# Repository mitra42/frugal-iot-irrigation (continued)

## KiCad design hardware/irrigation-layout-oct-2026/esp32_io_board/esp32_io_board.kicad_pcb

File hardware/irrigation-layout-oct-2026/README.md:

# Frugal-IoT Irrigation V0.2 — valve-driver board (branch `uln2803`)

> **This branch replaces the V0.1 board's four relays with MOSFETs driving 12 V DC solenoid valves directly**
> (DECISIONS D67–D78; a ULN2803A was tried first and dropped, D70). Eight valve outputs, D75. Phase 1 (schematic,
> BOM, cost) and Phase 2 (layout, D79–D86) are done, and the power parts now match the LoRa board (D87–D90): the
> PCB, PCB-LAYOUT.pdf and `fabrication/` are the valve board, laid out, routed and DRC clean (21 Nov 2026),
> **for review — not yet ordered or built**.

An ESP32 I/O board for irrigation and similar field control: eight 12 V DC valve outputs, RS485 (Modbus), I2C sensors,
two spare GPIOs, and power from 12 V, USB or a single LiPo cell. Designed Oct 2026 for assembly by JLCPCB.
This folder is for review: comments and suggested changes welcome — see "Points for reviewers" below.

## The board

- 100 × 62 mm (the relay board was 100 × 80), 2 layers, 1.6 mm FR-4, 4 × M3 corner holes.
- The eight valve terminals (5.08 mm, butted into one 81 mm row) along the bottom long edge, each channel's MOSFET,
  flyback diode and LED in a column straight above its terminal; 12 V in on the left edge beside them; field
  connectors (RS485, I2C, GPIOs, OLED) along the top edge; USB-C on the right short edge, LiPo connector on the left.
- The valve current has its own copper (D82): 2 mm from the 12 V terminal through the fuse and diode, a 2 mm
  +12V bus on the bottom layer along the terminal row, and 1 mm from each MOSFET straight down to its terminal.
- Surface-mount parts on the top side, assembled by JLCPCB; terminals and headers are through-hole
  (JLCPCB hand-solders them, or you can).

## Power

- Powered from **12 V** (screw terminal, up to 15 V), **5 V USB-C**, or a **local single LiPo cell** (optional,
  JST-PH, 18650 at most).
- 12 V input: 3 A resettable fuse, reverse-polarity protection (5 A Schottky), 15 V TVS, then a 5 V buck (AP63205). USB 5 V and the
  buck output are diode-ORed onto the 5 V rail, so either or both can be connected.
- The 5 V rail charges the cell (TP4056; 250 mA, or 500 mA with a solder jumper). The cell has its own
  protection (XB5353A, one chip with its MOSFETs inside: over-charge 4.30 V, over-discharge 2.4 V,
  3 A over-current/short), as on the LoRa board.
- Load sharing: when 5 V is present it powers the board and the charger only charges; when 5 V goes away a
  P-FET switches the cell in. Either source then feeds a 3.3 V LDO (RT9080, 600 mA, 2 µA quiescent) for the
  module.
- Two switched rails turned on together by one GPIO: **3V3_SW** (sensors, I2C, RS485) and **5V_SW** (RS485
  sensor supply). Both off at reset. 5V_SW only exists when 12 V or USB is present, not on battery alone.
- Monitoring: the 12 V input and the cell voltage are each read on an ADC pin.
- The valves run from 12 V, so **valves work only when 12 V is connected**.
- Test pads TP1–TP9 on every supply rail (+12V, +5V, VBUS, VBAT, VSYS, +3V3, +3V3_SW, +5V_SW) and GND, each
  labelled on the silkscreen with its rail, for a meter probe or a soldered wire.

## Processor

- ESP32-C6-MINI-1U module (default) or ESP32-C3-MINI-1U on the same footprint — both have a **U.FL antenna
  socket** (an external antenna is needed). Two pairs of 0 Ω links select which module's USB pins are used.
- Native USB on USB-C for programming and serial (no USB-UART chip); USB ESD protection.
- Buttons: RESET, BOOT/BTN1 (hold at reset for download mode, a normal button afterwards), BTN2 (C6 only).
- Status LED (green); charger LEDs (charging red, charged green).
- Unfitted headers for UART0 debug and a cell thermistor.

## Outputs and interfaces

- **8 valve outputs** for 12 V DC solenoid valves (channels 5–8 can be left unfitted to save ~$0.21–0.29 each), each a 2-way 5.08 mm terminal: V+ (+12V) and OUT (switched
  to ground). One AO3400A MOSFET per valve with a 100k gate pull-down and an SS34 flyback diode returned to
  the same +12V as the V+ pins (D69, D73). **Up to ~2 A per valve**, any number at once; total from 12 V IN
  limited to ~3 A by the input fuse F1 (D77). Fit an inline fuse at the battery too. Pumps can be driven too. Not for latching (pulse) valves or 24 V AC
  valves. Driven through an I2C I/O expander (TCA9534); the pull-downs keep the valves off through reset
  and boot. A red LED per valve shows it is on.
- **RS485** (Modbus): 3.3 V transceiver, not isolated, transmit/receive switched automatically from the TX
  line; bias resistors, 120 Ω termination on a solder jumper, surge protection. Terminal: 5V_SW, A, B, GND.
- **I2C**: 4-way 2.54 mm terminal (3V3_SW, SDA, SCL, GND) plus a 4-pin OLED header (GND, 3V3_SW, SCL, SDA).
- **2 GPIOs** (GPIO_A — ADC capable — and GPIO_B, C6 only) on 2-way 2.54 mm terminals with GND, with
  unfitted pull-up/pull-down positions.

## Firmware notes

- Turn on RAIL_EN before any I2C traffic (valve changes included) or RS485; the expander itself is always
  powered and keeps the valves as set while the rail is off.
- Valve outputs: TCA9534 P0–P7 high = valve 1–8 on (P0–P3 as on the relay board, so no firmware change for those). Terminals J11–J18; RS485 is now J10.
- GPIO map (module pad → use) is in DECISIONS.md, D18.

## Points for reviewers

Items that are deliberately "proposed" rather than final — opinions especially welcome:

1. RS485 direction from TX (D21): fine for Modbus at 9600 baud, marginal with long cables and two
   terminations; a true auto-direction transceiver (THVD1406) is the alternative.
2. RS485 terminal supplies 5V_SW — should it be 12 V for your sensors? (D22)
3. Cell thermistor (TEMP) disabled by default (D27); charge current 250/500 mA (D12).
4. LiPo connector: pin 1 = −, pin 2 = + (D47). JST-PH polarity is not standard — check your cells.
5. Valve outputs (D73): ~2 A per valve, ~3 A total from 12 V IN, where F1, a 3 A resettable fuse, trips on a short (D77). Enough for your valves
   and any pump?
6. The 5.08 mm terminals use the Phoenix MKDS footprint for KF128 parts of the same pitch (D42).
7. Small bulk capacitance on 3V3_SW to limit inrush (D33).
8. Before ordering: check part rotations in JLCPCB's assembly preview (see fabrication/README.md).

## Cost (JLCPCB, Nov 2026)

About **$21.04 per board for 10**, **$12.07 per board for 100**, assembled, before shipping, with all eight
valve channels fitted and the input fuse (JLCPCB prices of 21 Nov 2026; the four-relay design is $22.04 / $12.63).
The bare PCB for the 100 × 62 mm board is estimated from the 100 × 80 mm quote, not yet re-quoted (D86): the
smaller board saves nothing at 10 and about $0.13 per board at 100.
Breakdown in COST-ESTIMATE.txt; the ESP32 module is the largest single item.

## What's in this folder

| | |
|---|---|
| `README.md` | This description |
| `SCHEMATIC.pdf` | Full schematic, one sheet |
| `PCB-LAYOUT.pdf` | 3D views and both copper layers |
| `BOM.csv` | Bill of materials with LCSC (JLCPCB) part numbers |
| `COST-ESTIMATE.txt` | JLCPCB cost for 10 and 100 boards |
| `DECISIONS.md` | Every design decision, why, and what would reopen it (D1–D90) |
| `esp32_io_board/` | KiCad 10 project (schematic, PCB, project libraries) |
| `fabrication/` | Files to order from JLCPCB — see its README |
| `firmware/` | PlatformIO env for frugal-iot-irrigation + board variant (pins_arduino.h) |
| `datasheets/` | Datasheets checked during design |
| `claude-tools/` | Scripts Claude uses to regenerate and change the design — reviewers can ignore |

To suggest a change: mark up the PDFs, edit in KiCad, or describe it; the schematic is generated from
`claude-tools/schematic/circuit.py`, so changes made by Claude go there rather than into the .kicad_sch.

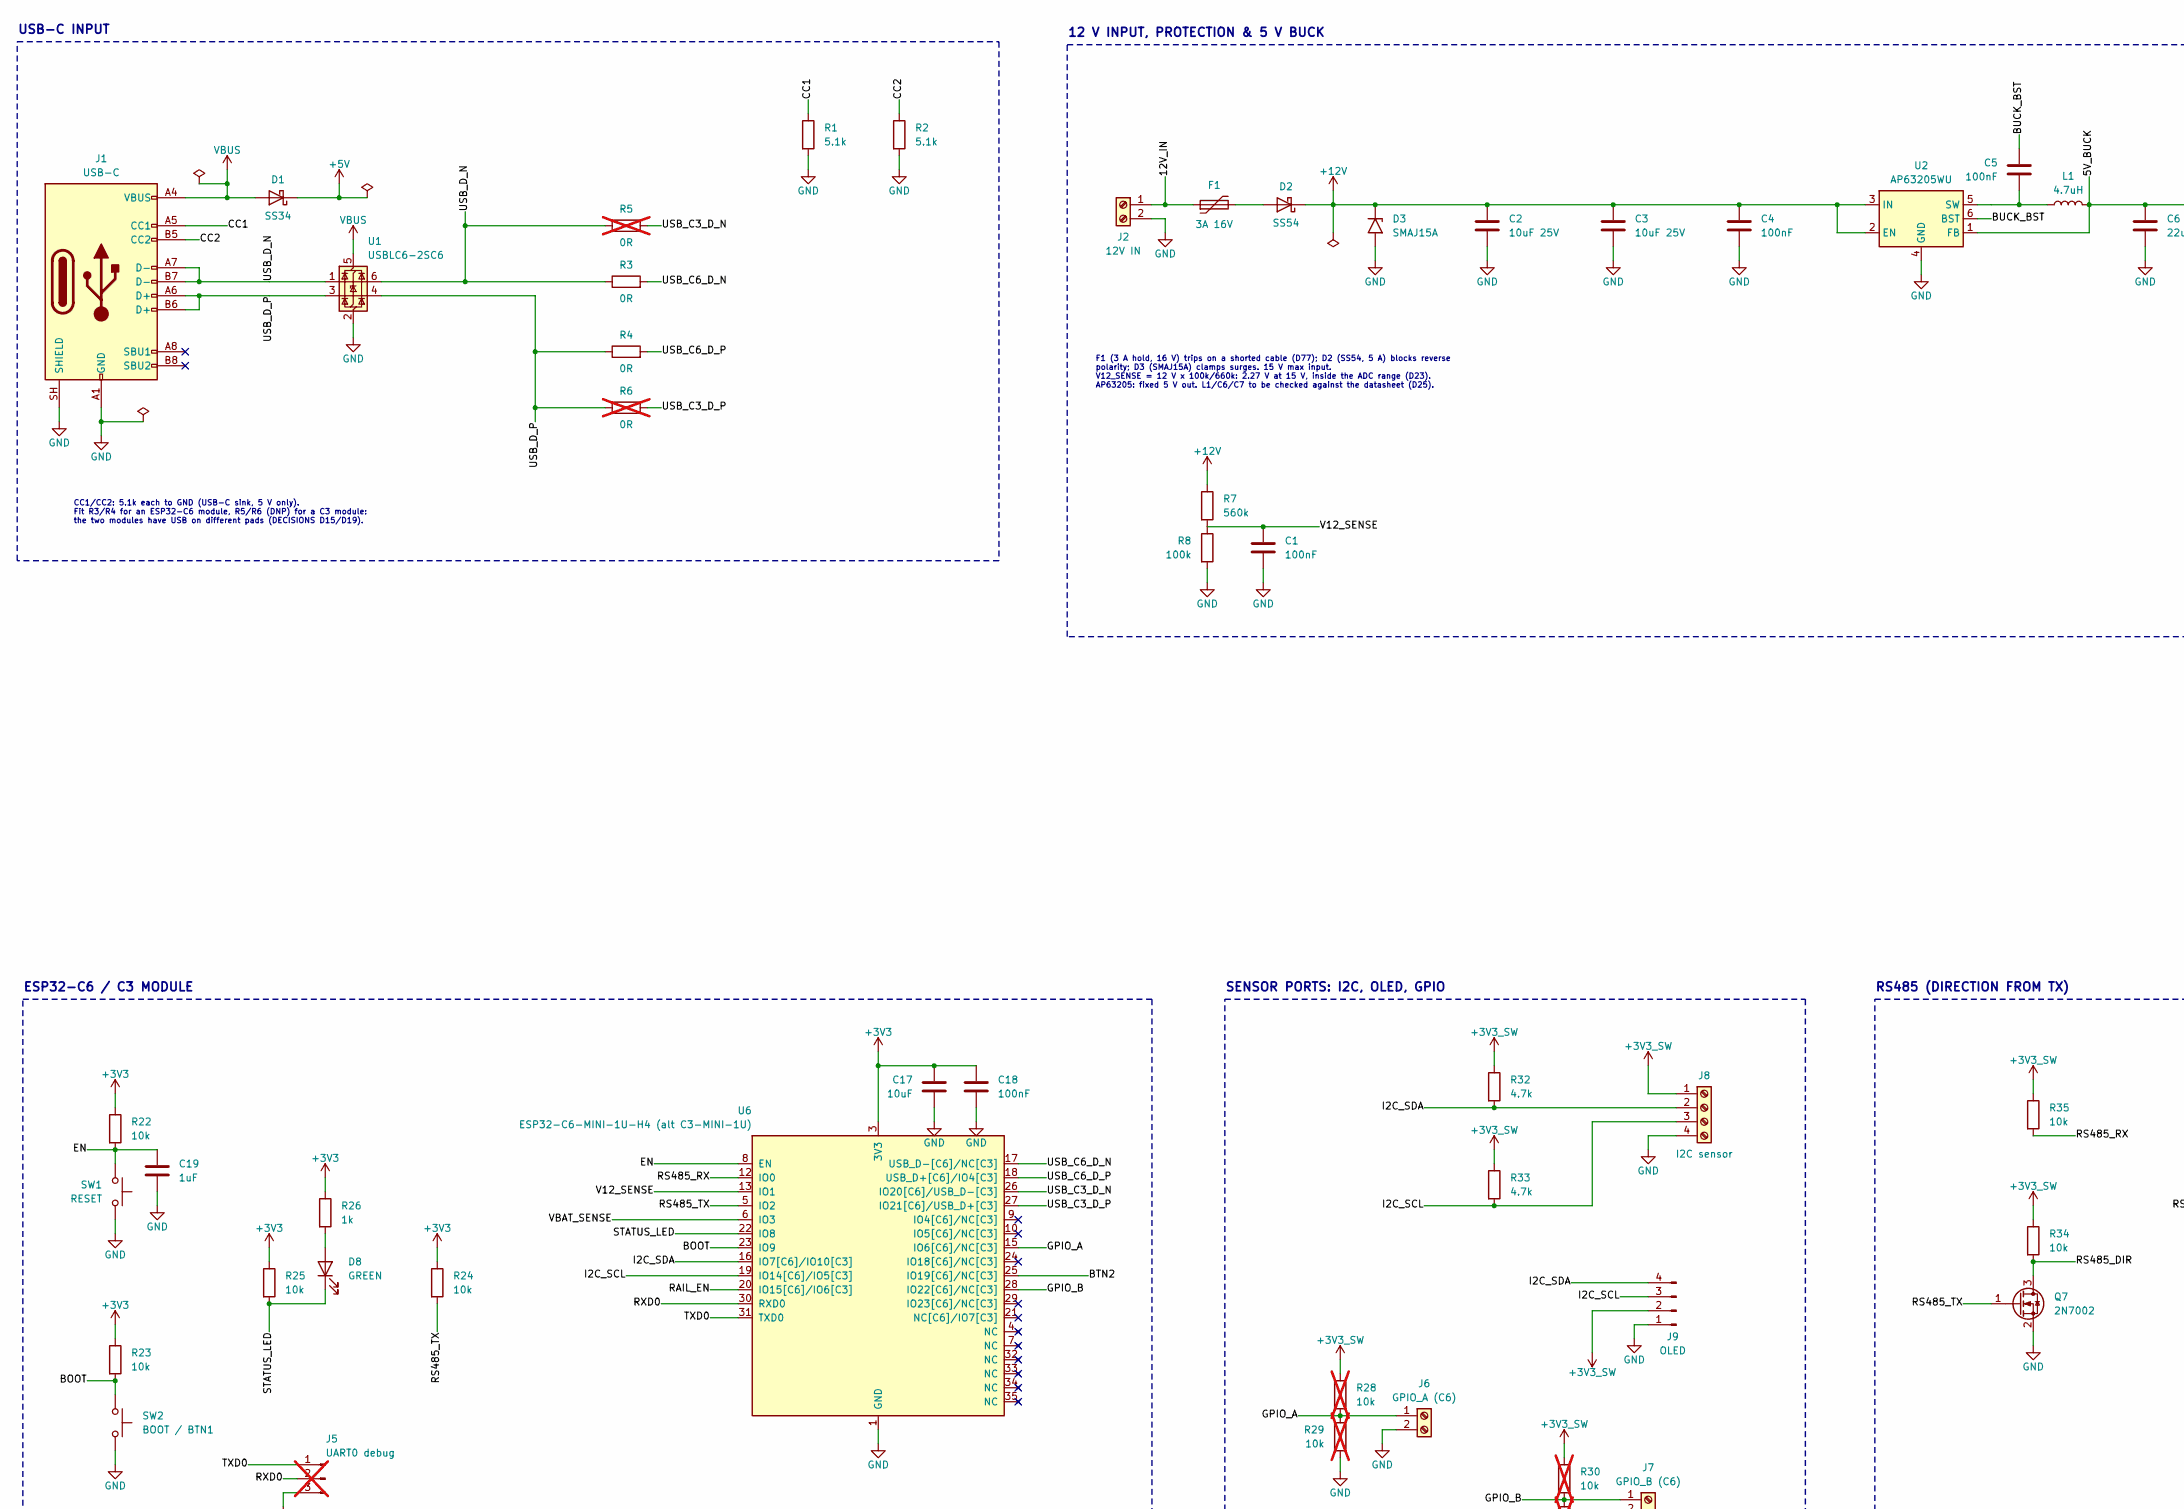
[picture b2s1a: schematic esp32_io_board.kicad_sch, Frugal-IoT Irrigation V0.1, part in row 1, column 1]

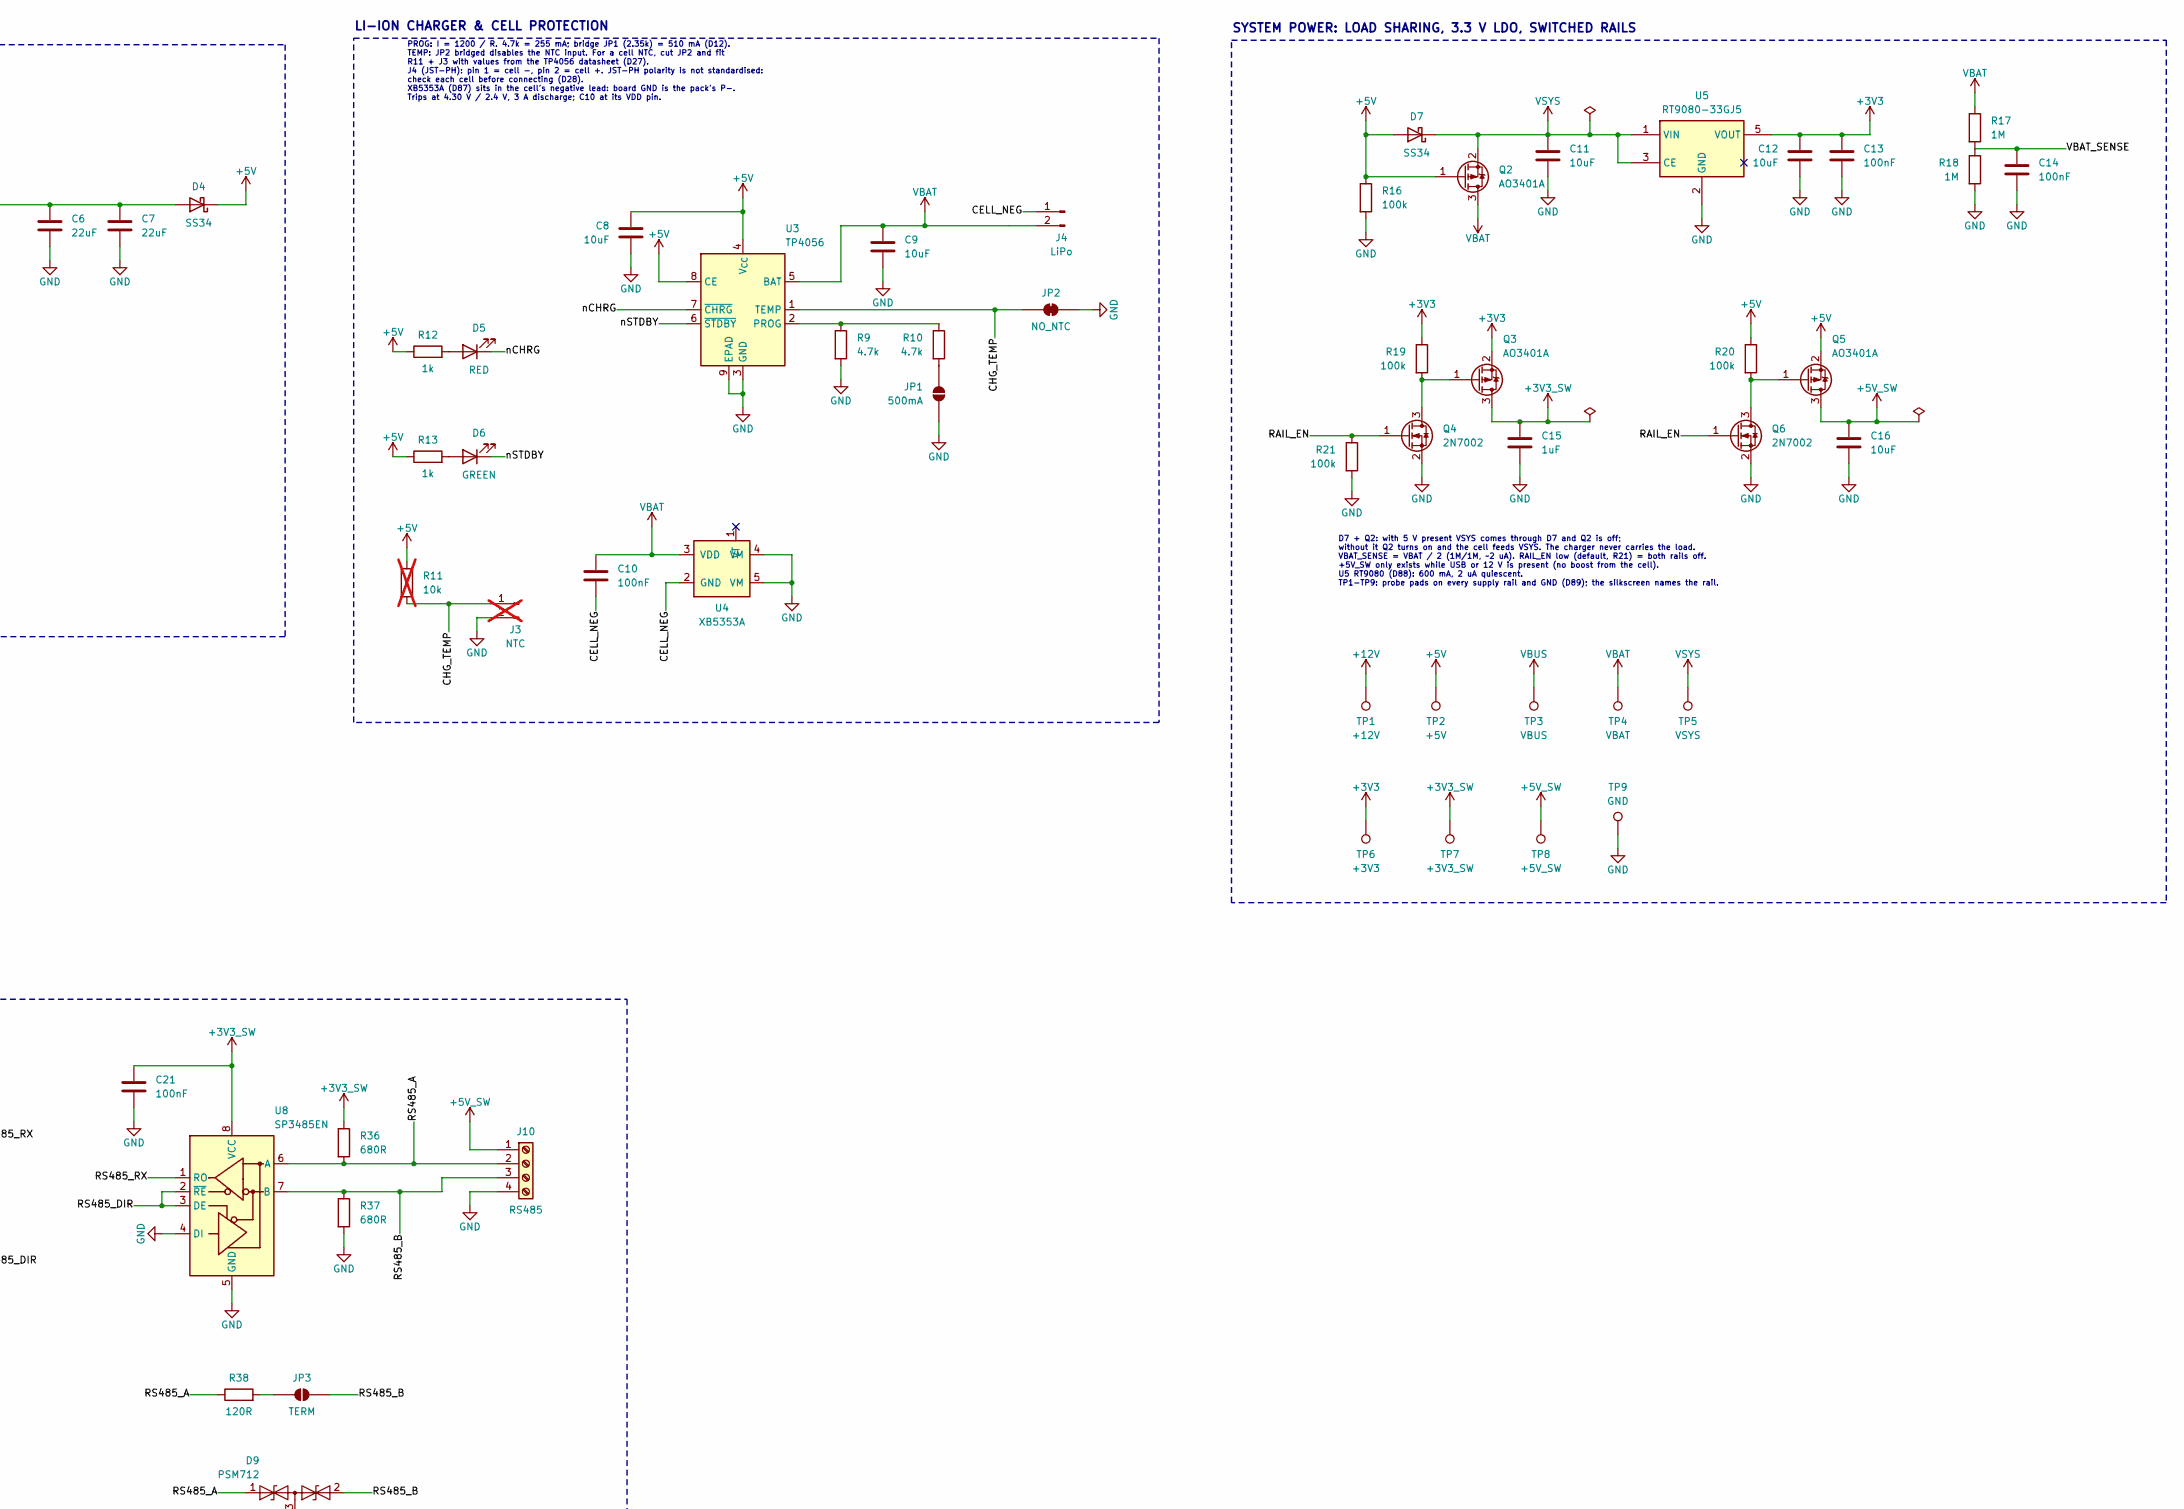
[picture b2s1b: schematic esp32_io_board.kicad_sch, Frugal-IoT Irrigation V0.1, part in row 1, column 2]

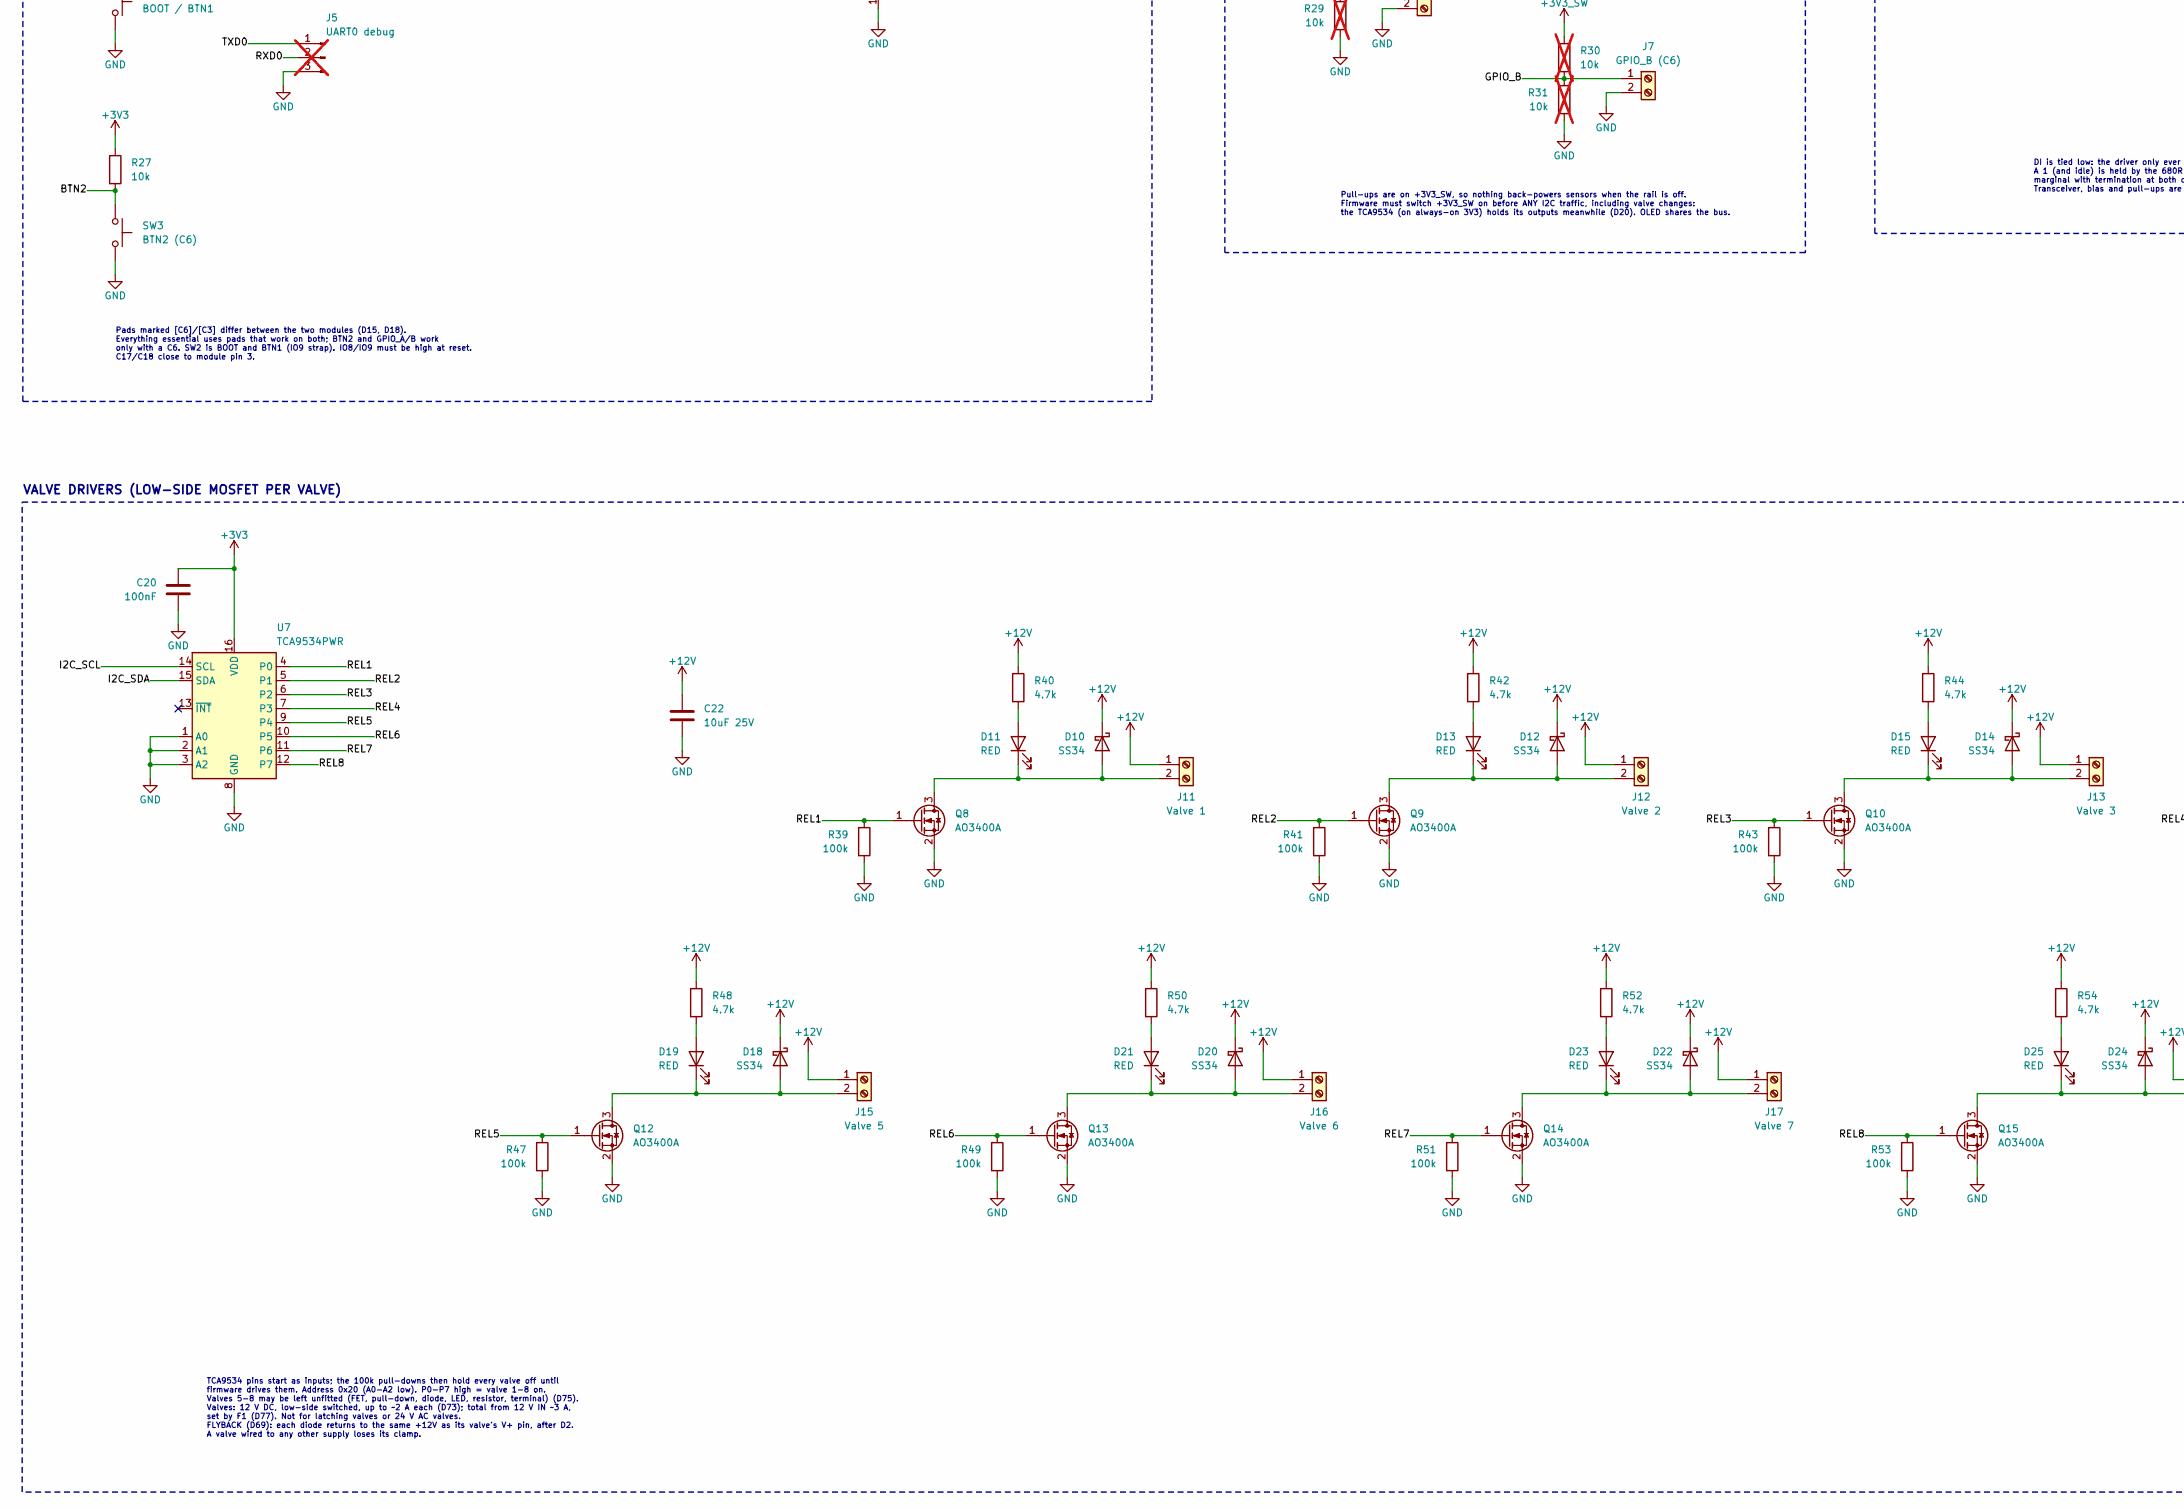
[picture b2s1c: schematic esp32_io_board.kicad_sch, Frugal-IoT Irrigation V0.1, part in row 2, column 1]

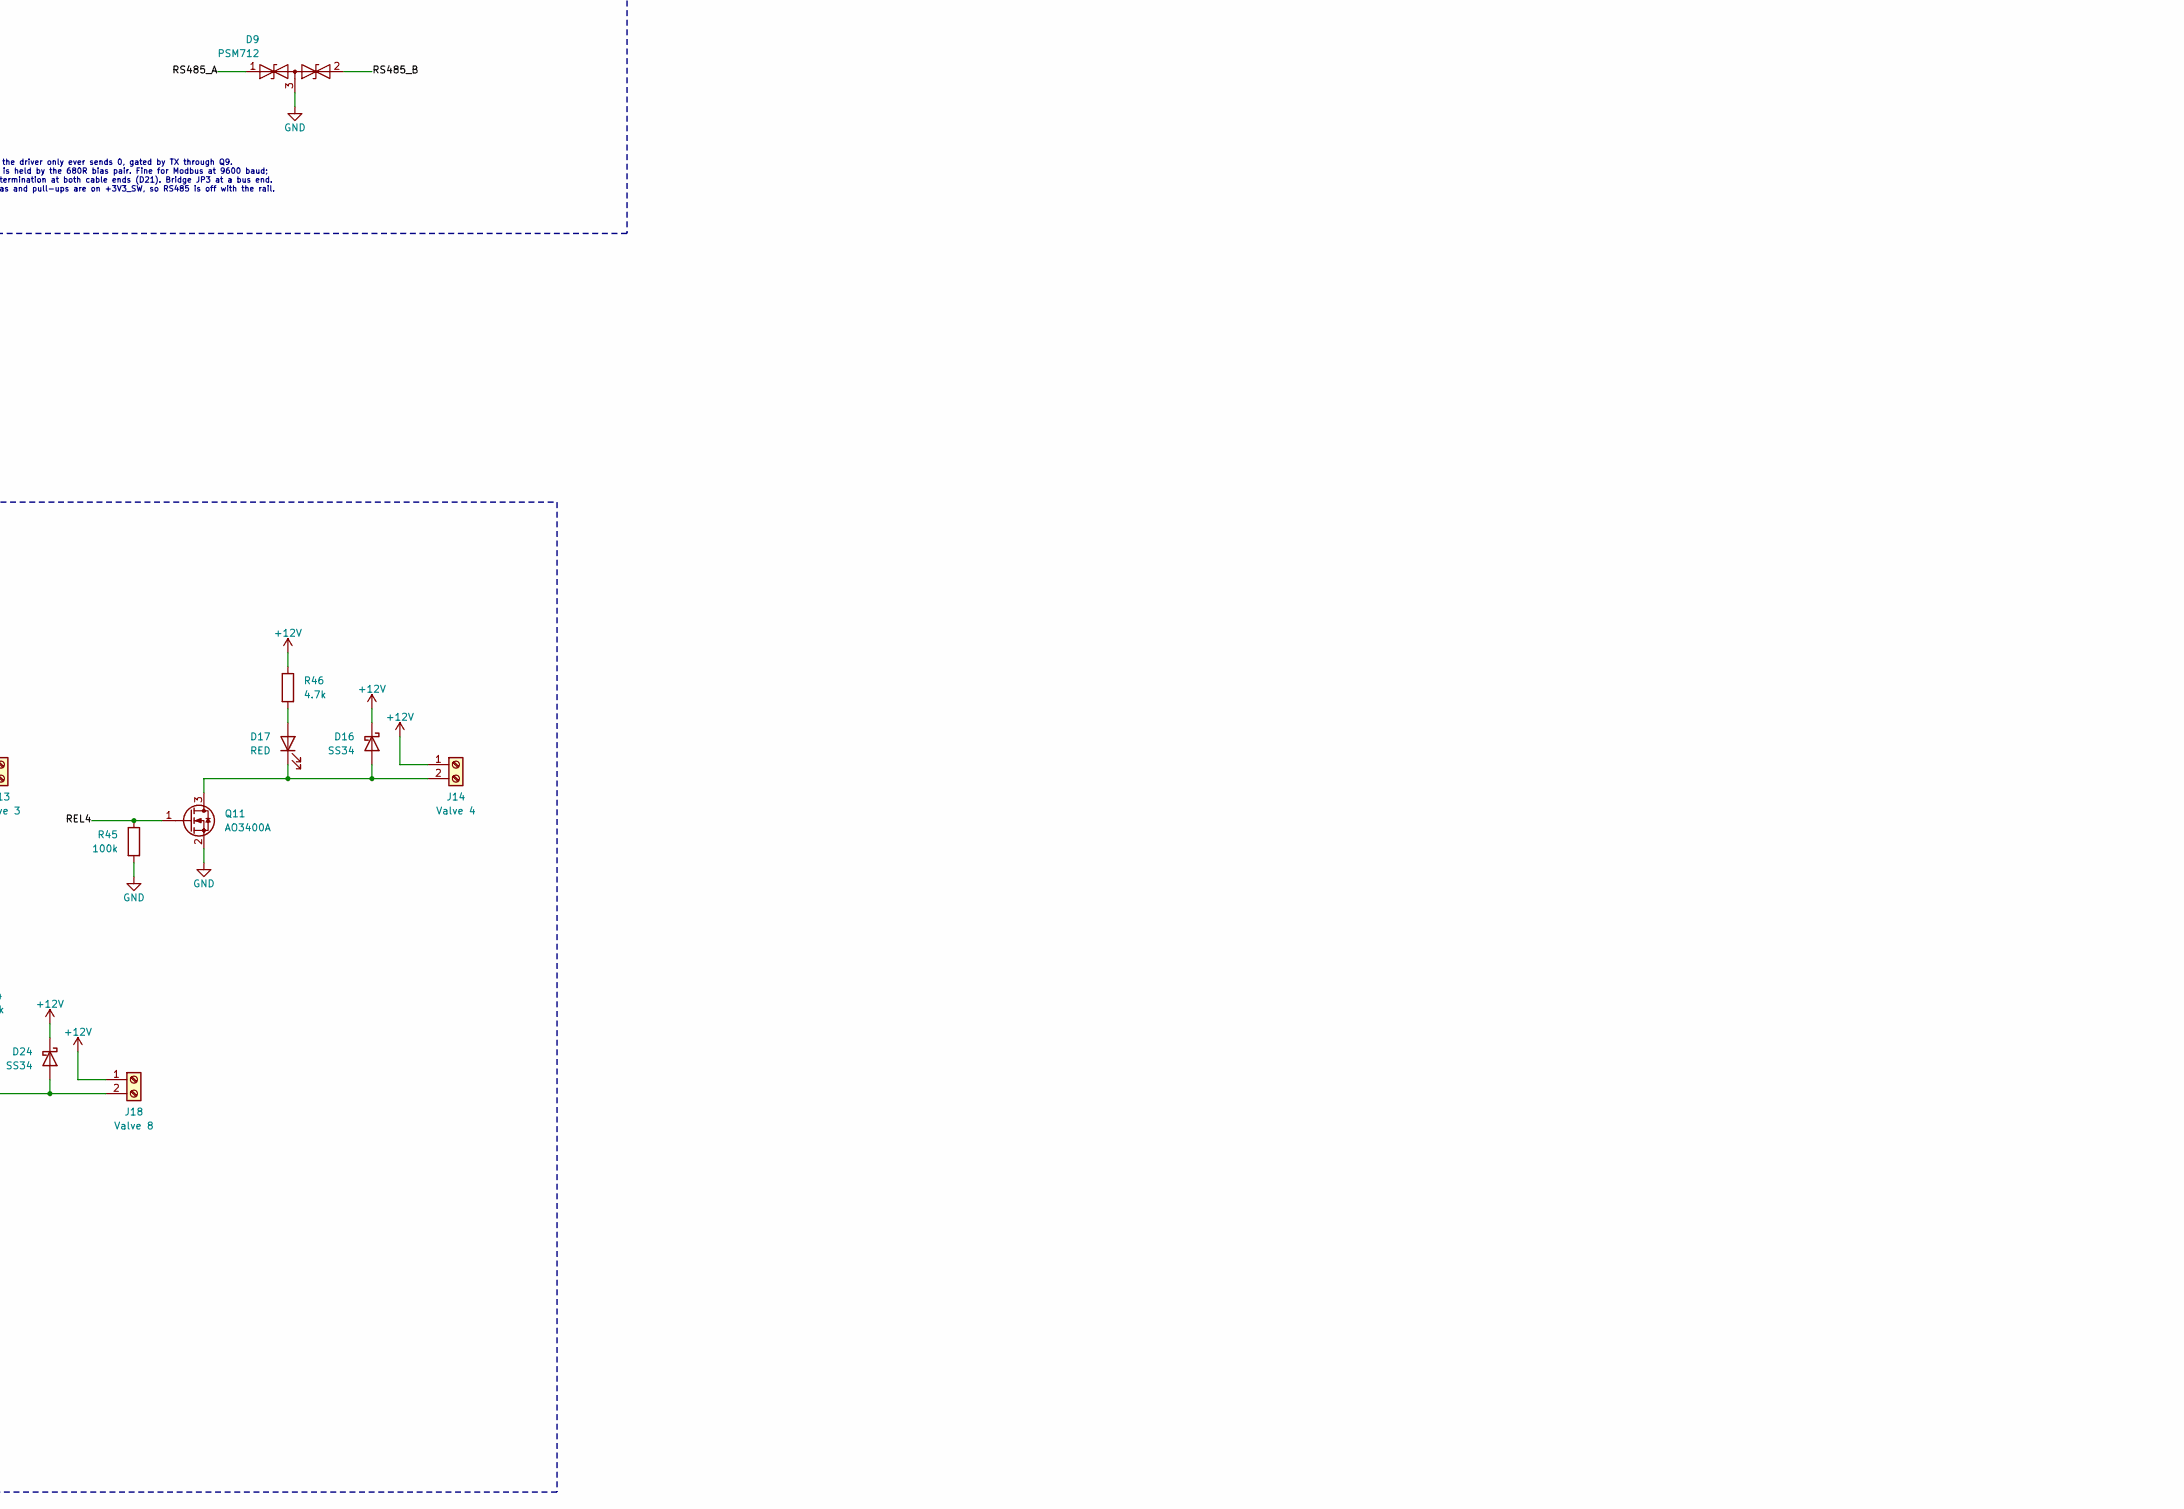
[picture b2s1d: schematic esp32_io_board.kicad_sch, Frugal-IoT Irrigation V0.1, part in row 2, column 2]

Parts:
C1, C4, C5, C10, C13, C14, C18, C20, C21: 100nF; C_0603_1608Metric; MPN 100nF; LCSC C14663
C2, C3, C22: 10uF 25V; C_1206_3216Metric; MPN 10uF 25V; LCSC C13585
C6, C7: 22uF; C_1206_3216Metric; MPN 22uF; LCSC C12891
C8, C9, C11, C12, C16, C17: 10uF; C_0603_1608Metric; MPN 10uF; LCSC C19702
C15, C19: 1uF; C_0603_1608Metric; MPN 1uF; LCSC C15849
D1, D4, D7, D10, D12, D14, D16, D18, D20, D22, D24: SS34; D_SMA; MPN SS34; LCSC C8678
D2: SS54; D_SMA; MPN SS54; LCSC C22452
D3: SMAJ15A; D_SMA; MPN SMAJ15A; LCSC C19077535
D5, D11, D13, D15, D17, D19, D21, D23, D25: RED; LED_0603_1608Metric; MPN KT-0603R; LCSC C2286
D6, D8: GREEN; LED_0805_2012Metric; MPN KT-0805G; LCSC C2297
D9: PSM712; SOT-23; MPN PSM712-LF-T7; LCSC C32677
F1: 3A 16V; Fuse_1812_4532Metric; MPN SMD1812P300TF/16; LCSC C702820
J1: USB-C; USB_C_Receptacle_HRO_TYPE-C-31-M-12; MPN TYPE-C-31-M-12; LCSC C165948
J2: 12V IN; TerminalBlock_KF128-5.08-2P; MPN KF128-5.08-2P; LCSC C474952
J3: NTC; PinHeader_1x02_P2.54mm_Vertical; MPN NTC; not fitted
J4: LiPo; JST_PH_S2B-PH-K_1x02_P2.00mm_Horizontal; MPN S2B-PH-K-S; LCSC C157932
J5: UART0 debug; PinHeader_1x03_P2.54mm_Vertical; MPN UART0 debug; not fitted
J6: GPIO_A (C6); TerminalBlock_Xinya_XY308-2.54-2P_1x02_P2.54mm_Horizontal; MPN XY308-2.54-2P; LCSC C557685
J7: GPIO_B (C6); TerminalBlock_Xinya_XY308-2.54-2P_1x02_P2.54mm_Horizontal; MPN XY308-2.54-2P; LCSC C557685
J8: I2C sensor; TerminalBlock_Xinya_XY308-2.54-4P_1x04_P2.54mm_Horizontal; MPN XY308-2.54-4P; LCSC C915913
J9: OLED; PinHeader_1x04_P2.54mm_Vertical; MPN PZ254V-11-04P; LCSC C492403
J10: RS485; TerminalBlock_Xinya_XY308-2.54-4P_1x04_P2.54mm_Horizontal; MPN XY308-2.54-4P; LCSC C915913
J11: Valve 1; TerminalBlock_KF128-5.08-2P; MPN KF128-5.08-2P; LCSC C474952
J12: Valve 2; TerminalBlock_KF128-5.08-2P; MPN KF128-5.08-2P; LCSC C474952
J13: Valve 3; TerminalBlock_KF128-5.08-2P; MPN KF128-5.08-2P; LCSC C474952
J14: Valve 4; TerminalBlock_KF128-5.08-2P; MPN KF128-5.08-2P; LCSC C474952
J15: Valve 5; TerminalBlock_KF128-5.08-2P; MPN KF128-5.08-2P; LCSC C474952
J16: Valve 6; TerminalBlock_KF128-5.08-2P; MPN KF128-5.08-2P; LCSC C474952
J17: Valve 7; TerminalBlock_KF128-5.08-2P; MPN KF128-5.08-2P; LCSC C474952
J18: Valve 8; TerminalBlock_KF128-5.08-2P; MPN KF128-5.08-2P; LCSC C474952
JP1: 500mA; SolderJumper-2_P1.3mm_Open_RoundedPad1.0x1.5mm; MPN 500mA
JP2: NO_NTC; SolderJumper-2_P1.3mm_Bridged_RoundedPad1.0x1.5mm; MPN NO_NTC
JP3: TERM; SolderJumper-2_P1.3mm_Open_RoundedPad1.0x1.5mm; MPN TERM
L1: 4.7uH; L_Sunlord_SWPA5040S; MPN SWPA5040S4R7NT; LCSC C305174
Q2, Q3, Q5: AO3401A; SOT-23; MPN AO3401A; LCSC C15127
Q4, Q6, Q7: 2N7002; SOT-23; MPN 2N7002; LCSC C8545
Q8, Q9, Q10, Q11, Q12, Q13, Q14, Q15: AO3400A; SOT-23; MPN AO3400A; LCSC C20917
R1, R2: 5.1k; R_0603_1608Metric; MPN 5.1k; LCSC C23186
R3, R4: 0R; R_0603_1608Metric; MPN 0R; LCSC C21189
R5, R6: 0R; R_0603_1608Metric; MPN 0R; LCSC C21189; not fitted
R7: 560k; R_0603_1608Metric; MPN 560k; LCSC C23203
R8, R16, R19, R20, R21, R39, R41, R43, R45, R47, R49, R51, R53: 100k; R_0603_1608Metric; MPN 100k; LCSC C25803
R9, R10, R32, R33, R40, R42, R44, R46, R48, R50, R52, R54: 4.7k; R_0603_1608Metric; MPN 4.7k; LCSC C23162
R11, R28, R29, R30, R31: 10k; R_0603_1608Metric; MPN 10k; LCSC C25804; not fitted
R12, R13, R26: 1k; R_0603_1608Metric; MPN 1k; LCSC C21190
R17, R18: 1M; R_0603_1608Metric; MPN 1M; LCSC C22935
R22, R23, R24, R25, R27, R34, R35: 10k; R_0603_1608Metric; MPN 10k; LCSC C25804
R36, R37: 680R; R_0603_1608Metric; MPN 680R; LCSC C23228
R38: 120R; R_0603_1608Metric; MPN 120R; LCSC C22787
SW1: RESET; SW_Push_1P1T_XKB_TS-1187A; MPN TS-1187A-B-A-B; LCSC C318884
SW2: BOOT / BTN1; SW_Push_1P1T_XKB_TS-1187A; MPN TS-1187A-B-A-B; LCSC C318884
SW3: BTN2 (C6); SW_Push_1P1T_XKB_TS-1187A; MPN TS-1187A-B-A-B; LCSC C318884
TP1: +12V; TestPoint_Pad_D1.5mm; MPN +12V
TP2: +5V; TestPoint_Pad_D1.5mm; MPN +5V
TP3: VBUS; TestPoint_Pad_D1.5mm; MPN VBUS
TP4: VBAT; TestPoint_Pad_D1.5mm; MPN VBAT
TP5: VSYS; TestPoint_Pad_D1.5mm; MPN VSYS
TP6: +3V3; TestPoint_Pad_D1.5mm; MPN +3V3
TP7: +3V3_SW; TestPoint_Pad_D1.5mm; MPN +3V3_SW
TP8: +5V_SW; TestPoint_Pad_D1.5mm; MPN +5V_SW
TP9: GND; TestPoint_Pad_D1.5mm; MPN GND
U1: USBLC6-2SC6; SOT-23-6; MPN USBLC6-2SC6; LCSC C7519
U2: AP63205WU; TSOT-23-6; MPN AP63205WU-7; LCSC C2071056
U3: TP4056; SOIC-8-1EP_3.9x4.9mm_P1.27mm_EP2.41x3.3mm; MPN TP4056; LCSC C16581
U4: XB5353A; SOT-23-5; MPN XB5353A; LCSC C80628
U5: RT9080-33GJ5; TSOT-23-5; MPN RT9080-33GJ5; LCSC C841192
U6: ESP32-C6-MINI-1U-H4 (alt C3-MINI-1U); ESP32-C3-C6-MINI-1U; MPN ESP32-C6-MINI-1U-H4; LCSC C20627095
U7: TCA9534PWR; TSSOP-16_4.4x5mm_P0.65mm; MPN TCA9534PWR; LCSC C783615
U8: SP3485EN; SOIC-8_3.9x4.9mm_P1.27mm; MPN SP3485EN-L/TR; LCSC C8963

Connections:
+3V3: C12.1, C13.1, C17.1, C18.1, C20.1, Q3.2 (S), R19.1, R22.1, R23.1, R24.1, R25.1, R26.1, R27.1, TP6.1, U5.5 (VOUT), U6.3 (3V3), U7.16 (VDD)
/5V_BUCK: C6.1, C7.1, D4.2 (A), L1.2, U2.1 (FB)
/12V_IN: F1.1, J2.1
/BOOT: R23.2, SW2.1, U6.23 (IO9)
/BTN2: R27.2, SW3.1, U6.25 (IO19[C6]/NC[C3])
/BUCK_BST: C5.1, U2.6 (BST)
/CC1: J1.A5 (CC1), R1.1
/CC2: J1.B5 (CC2), R2.1
/CELL_NEG: C10.2, J4.1, U4.2 (GND)
/CHG_TEMP: J3.1, JP2.1 (A), R11.2, U3.1 (TEMP)
/EN: C19.1, R22.2, SW1.1, U6.8 (EN)
/GPIO_A: J6.1, R28.2, R29.1, U6.15 (IO6[C6]/NC[C3])
/GPIO_B: J7.1, R30.2, R31.1, U6.28 (IO22[C6]/NC[C3])
/I2C_SCL: J8.3, J9.3, R33.2, U6.19 (IO14[C6]/IO5[C3]), U7.14 (SCL)
/I2C_SDA: J8.2, J9.4, R32.2, U6.16 (IO7[C6]/IO10[C3]), U7.15 (SDA)
/RAIL_EN: Q4.1 (G), Q6.1 (G), R21.1, U6.20 (IO15[C6]/IO6[C3])
/REL1: Q8.1 (G), R39.1, U7.4 (P0)
/REL2: Q9.1 (G), R41.1, U7.5 (P1)
/REL3: Q10.1 (G), R43.1, U7.6 (P2)
/REL4: Q11.1 (G), R45.1, U7.7 (P3)
/REL5: Q12.1 (G), R47.1, U7.9 (P4)
/REL6: Q13.1 (G), R49.1, U7.10 (P5)
/REL7: Q14.1 (G), R51.1, U7.11 (P6)
/REL8: Q15.1 (G), R53.1, U7.12 (P7)
/RS485_A: D9.1 (A1), J10.2, R36.2, R38.1, U8.6 (A)
/RS485_B: D9.2 (A2), J10.3, JP3.2 (B), R37.1, U8.7 (B)
/RS485_DIR: Q7.3 (D), R34.2, U8.2 (~RE), U8.3 (DE)
/RS485_RX: R35.2, U6.12 (IO0), U8.1 (RO)
/RS485_TX: Q7.1 (G), R24.2, U6.5 (IO2)
/RXD0: J5.2, U6.30 (RXD0)
/STATUS_LED: D8.1 (K), R25.2, U6.22 (IO8)
/TXD0: J5.1, U6.31 (TXD0)
/USB_C3_D_N: R5.2, U6.26 (IO20[C6]/USB_D-[C3])
/USB_C3_D_P: R6.2, U6.27 (IO21[C6]/USB_D+[C3])
/USB_C6_D_N: R3.2, U6.17 (USB_D-[C6]/NC[C3])
/USB_C6_D_P: R4.2, U6.18 (USB_D+[C6]/IO4[C3])
/USB_D_N: J1.A7 (D-), J1.B7 (D-), R3.1, R5.1, U1.1 (I/O1), U1.6 (I/O1)
/USB_D_P: J1.A6 (D+), J1.B6 (D+), R4.1, R6.1, U1.3 (I/O2), U1.4 (I/O2)
/V12_SENSE: C1.1, R7.2, R8.1, U6.13 (IO1)
/VBAT_SENSE: C14.1, R17.2, R18.1, U6.6 (IO3)
/nCHRG: D5.1 (K), U3.7 (~CHRG)
/nSTDBY: D6.1 (K), U3.6 (~STDBY)
unnamed: D2.2 (A), F1.2
unnamed: D5.2 (A), R12.2
unnamed: D6.2 (A), R13.2
unnamed: D8.2 (A), R26.2
unnamed: D10.2 (A), D11.1 (K), J11.2, Q8.3 (D)
unnamed: D11.2 (A), R40.2
unnamed: D12.2 (A), D13.1 (K), J12.2, Q9.3 (D)
unnamed: D13.2 (A), R42.2
unnamed: D14.2 (A), D15.1 (K), J13.2, Q10.3 (D)
unnamed: D15.2 (A), R44.2
unnamed: D16.2 (A), D17.1 (K), J14.2, Q11.3 (D)
unnamed: D17.2 (A), R46.2
unnamed: D18.2 (A), D19.1 (K), J15.2, Q12.3 (D)
unnamed: D19.2 (A), R48.2
unnamed: D20.2 (A), D21.1 (K), J16.2, Q13.3 (D)
unnamed: D21.2 (A), R50.2
unnamed: D22.2 (A), D23.1 (K), J17.2, Q14.3 (D)
unnamed: D23.2 (A), R52.2
unnamed: D24.2 (A), D25.1 (K), J18.2, Q15.3 (D)
unnamed: D25.2 (A), R54.2
unnamed: JP1.1 (A), R10.2
unnamed: JP3.1 (A), R38.2
unnamed: Q3.1 (G), Q4.3 (D), R19.2
unnamed: Q5.1 (G), Q6.3 (D), R20.2
unnamed: C5.2, L1.1, U2.5 (SW)
unnamed: R9.1, R10.1, U3.2 (PROG)
VBAT: C9.1, C10.1, J4.2, Q2.3 (D), R17.1, TP4.1, U3.5 (BAT), U4.3 (VDD)

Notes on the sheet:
SYSTEM POWER: LOAD SHARING, 3.3 V LDO, SWITCHED RAILS
Pads marked [C6]/[C3] differ between the two modules (D15, D18). Everything essential uses pads that work on both; BTN2 and GPIO_A/B work only with a C6. SW2 is BOOT and BTN1 (IO9 strap). IO8/IO9 must be high at reset. C17/C18 close to module pin 3.
SENSOR PORTS: I2C, OLED, GPIO
TCA9534 pins start as inputs; the 100k pull-downs then hold every valve off until firmware drives them. Address 0x20 (A0-A2 low). P0-P7 high = valve 1-8 on. Valves 5-8 may be left unfitted (FET, pull-down, diode, LED, resistor, terminal) (D75). Valves: 12 V DC, low-side switched, up to ~2 A each (D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
RS485 (DIRECTION FROM TX)
DI is tied low: the driver only ever sends 0, gated by TX through Q9. A 1 (and idle) is held by the 680R bias pair. Fine for Modbus at 9600 baud; marginal with termination at both cable ends (D21). Bridge JP3 at a bus end. Transceiver, bias and pull-ups are on +3V3_SW, so RS485 is off with the rail.
ESP32-C6 / C3 MODULE
F1 (3 A hold, 16 V) trips on a shorted cable (D77); D2 (SS54, 5 A) blocks reverse polarity; D3 (SMAJ15A) clamps surges. 15 V max input. V12_SENSE = 12 V x 100k/660k: 2.27 V at 15 V, inside the ADC range (D23). AP63205: fixed 5 V out. L1/C6/C7 to be checked against the datasheet (D25).
D7 + Q2: with 5 V present VSYS comes through D7 and Q2 is off; without it Q2 turns on and the cell feeds VSYS. The charger never carries the load. VBAT_SENSE = VBAT / 2 (1M/1M, ~2 uA). RAIL_EN low (default, R21) = both rails off. +5V_SW only exists while USB or 12 V is present (no boost from the ce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
Pull-ups are on +3V3_SW, so nothing back-powers sensors when the rail is off. Firmware must switch +3V3_SW on before ANY I2C traffic, including valve changes: the TCA9534 (on always-on 3V3) holds its outputs meanwhile (D20). OLED shares the bus.
USB-C INPUT
VALVE DRIVERS (LOW-SIDE MOSFET PER VALVE)
CC1/CC2: 5.1k each to GND (USB-C sink, 5 V only). Fit R3/R4 for an ESP32-C6 module, R5/R6 (DNP) for a C3 module: the two modules have USB on different pads (DECISIONS D15/D19).
LI-ION CHARGER & CELL PROTECTION
12 V INPUT, PROTECTION & 5 V BUCK
PROG: I = 1200 / R. 4.7k = 255 mA; bridge JP1 (2.35k) = 510 mA (D12). TEMP: JP2 bridged disables the NTC input. For a cell NTC, cut JP2 and fit R11 + J3 with values from the TP4056 datasheet (D27). J4 (JST-PH): pin 1 = cell -, pin 2 = cell +. JST-PH polarity is not standardised: check each cell bef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
